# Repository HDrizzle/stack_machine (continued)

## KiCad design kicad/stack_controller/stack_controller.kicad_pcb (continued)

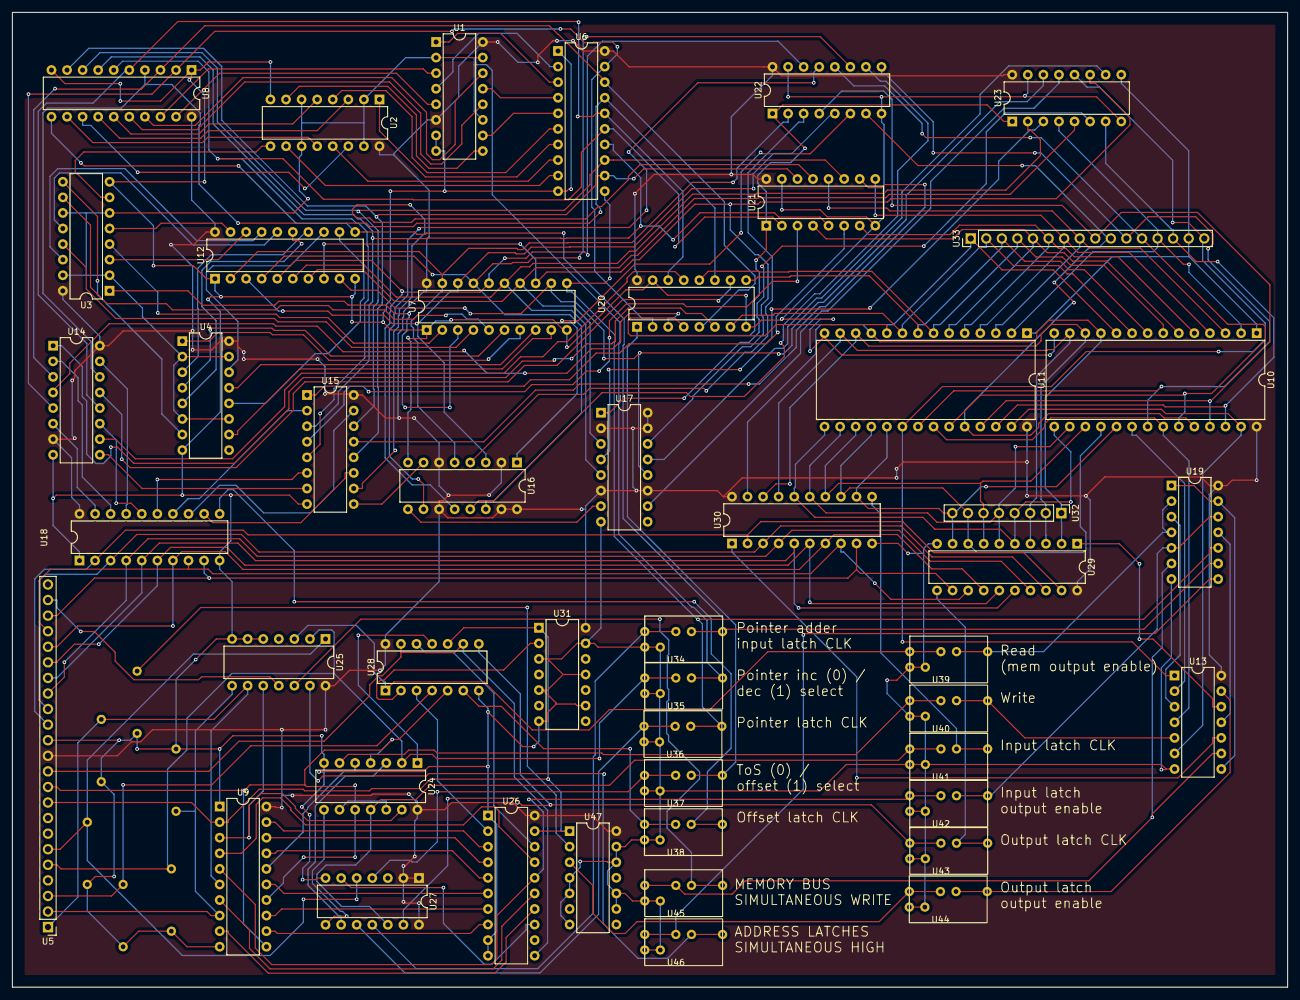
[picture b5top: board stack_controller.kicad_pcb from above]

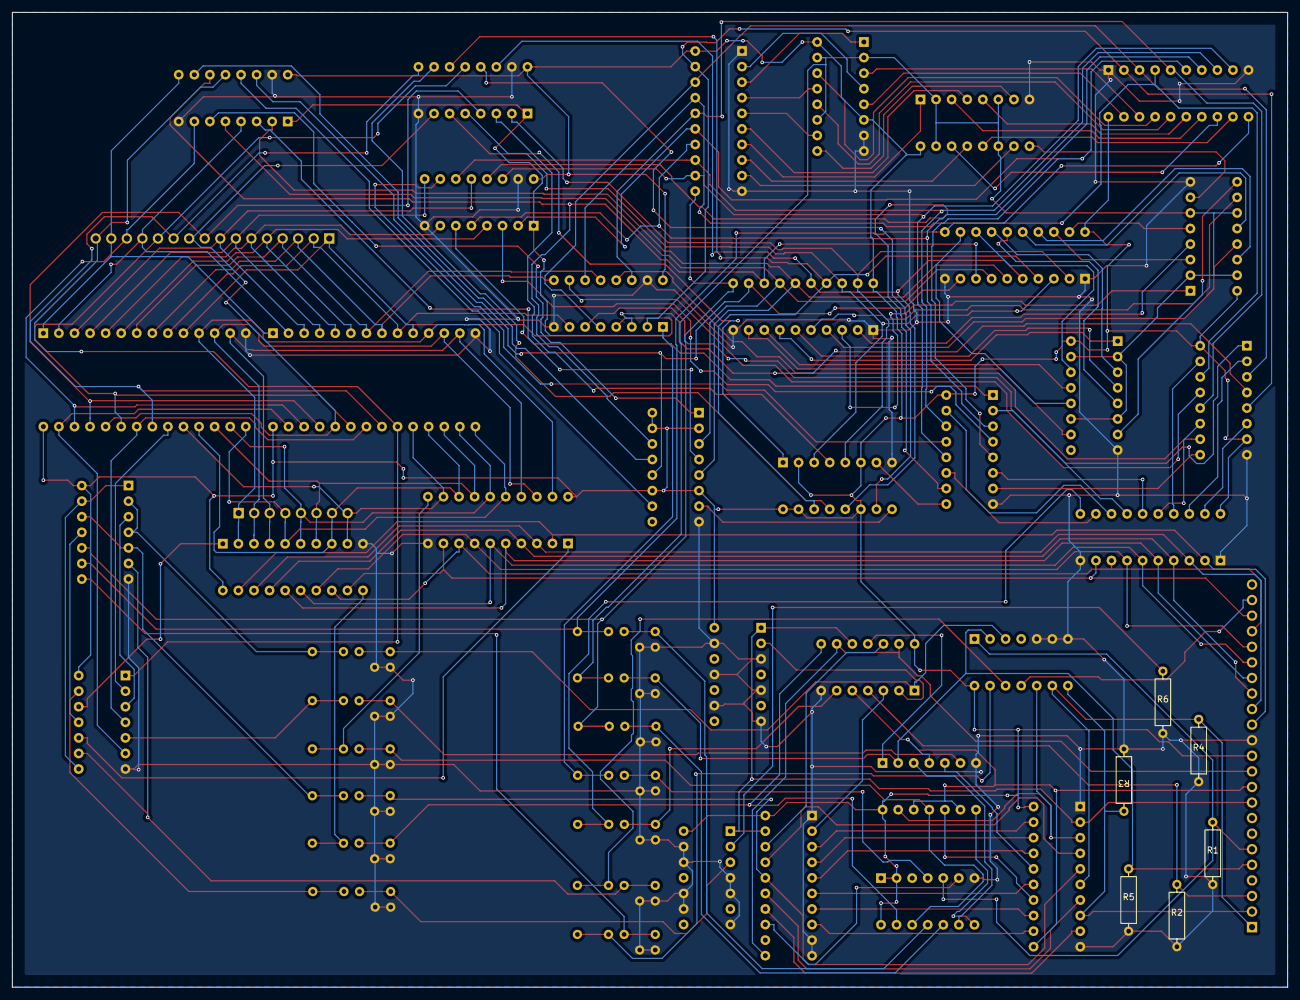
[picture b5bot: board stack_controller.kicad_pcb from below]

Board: 2 copper layers, 208.0 x 159.0 mm, 53 parts (6 on the bottom side), 174 nets.

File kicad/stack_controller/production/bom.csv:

Designator,Footprint,Quantity,Value,LCSC Part #
"R1, R2, R3, R4, R5, R6",0.4_pitch_resistor,6,1k,
"U1, U14, U15, U16, U17, U2, U20, U21, U22, U23, U3, U4",DIP-16_W7.62mm,12,~,
"U10, U11",DIP-28_W15.24mm,2,~,
"U12, U18, U26, U29, U30, U6, U7, U8, U9",DIP-20_W7.62mm,9,~,
"U13, U19, U24, U25, U27, U28, U31, U47",DIP-14_W7.62mm,8,~,
U32,PinHeader_1x08_P2.54mm_Vertical,1,~,
U33,PinHeader_1x16_P2.54mm_Vertical,1,~,
"U34, U35, U36, U37, U38, U39, U40, U41, U42, U43, U44, U45, U46",jumper,13,~,
U5,PinHeader_1x23_P2.54mm_Vertical,1,~,

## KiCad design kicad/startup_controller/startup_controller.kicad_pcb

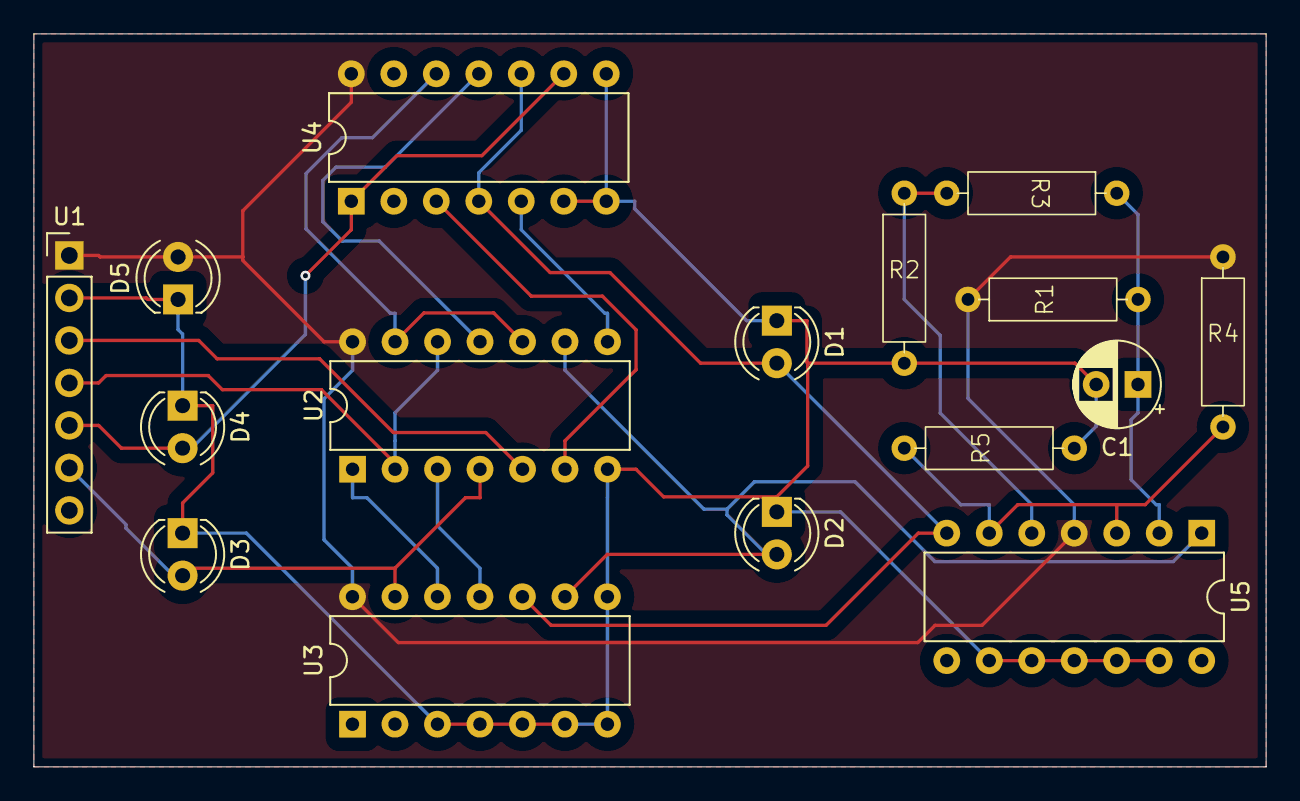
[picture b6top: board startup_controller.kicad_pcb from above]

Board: 2 copper layers, 73.7 x 43.8 mm, 16 parts (0 on the bottom side), 17 nets.

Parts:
C1: C; CP_Radial_D5.0mm_P2.50mm
D1, D2, D3, D4, D5: LED; LED_D4.0mm
R1, R2, R3, R4, R5: R; 0.4_pitch_resistor
U1: PinHeader_1x07_P2.54mm_Vertical
U2, U3, U4, U5: DIP-14_W7.62mm

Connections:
unnamed: D1.2 (A), U3.10 (1RESET), U4.4 (0RESET), U4.10 (1RESET), U5.7 (OUT_2)
unnamed: C1.2, D1.1 (K), D2.1 (K), D3.1 (K), D4.1 (K), D5.1 (K), R2.2, R5.2, U1.2 (GND), U2.7 (GND), U3.3 (0CLK), U3.4 (0RESET), U3.5 (0D), U3.6 (0SET), U3.7 (GND), U3.8 (1SET), U4.6 (0SET), U4.7 (GND), U4.8 (1SET), U5.9 (IN-_3), U5.10 (IN+_3), U5.11 (GND), U5.12 (IN+_4), U5.13 (IN-_4)
unnamed: D2.2 (A), U2.9 (4B), U3.9 (1D), U5.1 (OUT_1)
unnamed: D3.2 (A), U1.6 (ENABLE), U2.4 (2A), U3.13 (1Q)
unnamed: D4.2 (A), U1.5 (START), U4.1 (0Q), U4.9 (1D)
unnamed: D5.2 (A), R1.1, R4.1, U1.1 (V+), U2.14 (V+), U3.14 (V+), U4.14 (V+), U5.4 (V+)
unnamed: U1.3 (A_CLK), U2.5 (2B)
unnamed: U1.4 (B_CLK), U2.2 (1B), U2.12 (3B)
unnamed: U2.1 (1A), U3.12 (1Q3)
unnamed: U2.3 (1Q), U3.11 (1CLK)
unnamed: U2.6 (2Q), U4.3 (0CLK)
unnamed: U2.10 (4A), U2.13 (3A), U4.12 (1Q3)
unnamed: U2.11 (3Q), U4.11 (1CLK)
unnamed: U2.8 (4Q), U4.5 (0D)
unnamed: R4.2, R5.1, U5.3 (IN+_1), U5.6 (IN-_2)
unnamed: R2.1, R3.2, U5.5 (IN+_2)
unnamed: C1.1, R1.2, R3.1, U5.2 (IN-_1)
